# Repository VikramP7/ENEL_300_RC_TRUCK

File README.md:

*<div align="right"> Vikram Procter, Caleb Garcia, Graham Coleman, Devon Calvin | Feb 12, 2025 </div>*

# DIDSBURY DIDDLERS & Co. Est. 2006 - README

## Project Overview

Remote control car for our ENEL 300 design class at the Schulich School of Engineering at University of Calgary.

Our car integrates a variety of features including distance measurement, metal detection, togglable head/tail lights, tank steering, and more. These features are implemented through 3 custom PCBs, designed in Altium or KiCad. Wireless locomotion control and light control is implemented using the HC-05 Bluetooth transceiver module. The physical design was inspired by a RAM 3500 Cummins 6.7 Twin Turbo and its stereotypical owner *(Devon)*. This allowed us to bring a part of Alberta culture to the academic environment through innovation and design.

## Team Dynamic
  
*Image of Team Members and Professors: Dr. Philippe Gray, Devon Calvin, Graham Coleman, Vikram Procter, Caleb Garcia, and Dr. Flavio Alegretti Ramos; respectively from left to right*

The workload of the various systems was divided amongst us based on interest and skill. Coleman was responsible for implementing metal detection and distance measurement, in addition to working on Bluetooth communications, and controller design. Procter was responsible for ECU, power regulation, inter-board communication, general code management and review. Garcia was responsible for software development, 3D design and printing, and product selection. Calvin was responsible for motor driver development, 3D design, and Bluetooth communications.

## Systems Overview

The block diagram shows the operating architecture of the RC truck describing the PCB boards connections to each other. There were four custom PCBs in which 3 were used in the final design. Each board design function and integration are described in detail in the sections bellow. 

All boards excluding the controller interface with each other using an I2C bus, the ECU acts as the master on the bus and the Sensor Board/Motor Control Board act as slaves on the bus. The Controller board interfaces with the ECU alone using USART over a Bluetooth connection.

The four boards include: 
- **Controller Board** | not utilized in the final design, but would have been used within the controller to offer UI to user.
- **ECU** | Electronics Control Board, acts to integrate functionality of all other boards along with power supply regulation.
- **Sensor Board** | Finds and relays metal detection and distance sensing data.
- **Motor Control Board** | Houses motor drivers and receives data for locomotion control of vehicle.

## Sensors Systems (Sensor Board)
### Metal Detector

The metal detection system is designed around a 555 timer IC and inductor capacitor (LC) circuit. The 555 timer produces an AC input in which the frequency response output varies with changes in inductance. By exposing the inductor coil placed on the bottom of the car to a copper sheet the inductance of the coil changes and the frequency of the output changes in response.

The sensor board uses a built in timer module of the AVR128DB28 to measure the frequency of the LC circuit. By tuning a threshold, the recorded frequency could be used to identify if the coil was exposed to metal. This information was then relayed over I<sup>2</sup>C to the ECU.

### Distance Sensor
An ultrasonic distance sensor was used to find the distance of the nearest object in front of the car. The Sensor Board interfaced with the ultrasonic providing the appropriate 10 microsecond trigger and recording the echo. This raw echo data was transmitted over I<sup>2</sup>C to the ECU.

*Render of Sensor Board PCB*

## Power Systems (ECU)
### Battery
The battery we selected has a capacity of 3000 mAh with a nominal voltage of 12.6V, this was used to supply power to all boards and the motors excluding the metal detection circuit. This battery consisted of 4 cells with integrated charging and level balancing technology.

Through estimates of maximum current draw, the runtime on one full charge was calculated to be 228 minutes. This battery was initially chosen as previously we had sourced higher power motors; these higher power motors made the battery selection more reasonable for runtime calculations. However, in switching motors we decided not to change our battery selection as it was still sufficient for operation.

### Voltage Regulation

*Custom Standard for Molex Connector*

To produce the voltage 5V and 3.3V lines linear dropout regulators (LDOs) were used. These regulators were placed on the ECU and using a custom Molex connector, voltage levels were distributed to other boards (motor control board, and sensor board).

### Power Switch
The power switch uses a PMOS high side switch topology to switch between three states: off, USB power, and battery power. For regular operation 12.6V battery is used, however for development and debugging 5V USB can be used. This switch system allows for isolation between the battery and USB for safe operation.

  *Image of ECU Showing Power Switch*

## Communications Systems (ECU + Others)
### Bluetooth USART

[*Image Cred.*](https://www.electronicwings.com/sensors-modules/bluetooth-module-hc-05-)

The ECU board and controller boards preformed wireless communications via a USART over Bluetooth communications module [HC-05](https://www.electronicwings.com/sensors-modules/bluetooth-module-hc-05-). The controller board would send movement control and light switch position data to the ECU board, describing positions of single axis joy sticks and if the lights should be on or not. The ECU board would send sensor data including distance and metal detection.

Three 8-bit data packets were sent from the controller. Two packets described the left and right joystick position encoded using sign magnitude. And the third packet contained the status of the light switch. 

One 8-bit packet was sent from the ECU to describe metal detection (most significant bit), and distance sensor data encoded in the 7 least significant bits. 

### I<sup>2</sup>C Inter-board Communication
An I<sup>2</sup>C bus was utilized between boards within the vehicle (ECU, Motor Board, and Sensor Board). Connection between boards was accomplished using the same custom Molex connector as described in the power regulation section.

The ECU hosted the I<sup>2</sup>C bus housing the pull-up resistors and acted as the master on the bus. The ECU would relay motor control data received from the controller board to the Motor Board. The ECU would request data from the Sensor Board, receiving distance and metal detection data. I<sup>2</sup>C communications is a non-blocking function within the super loop of all boards. 

I<sup>2</sup>C packets took a very similar form to USART packets over Bluetooth. The motor board would receive two 8-bit sign-magnitude packets one for each side of the vehicle. Two packets were received from the Sensor Board. The MSB of the first packet described the metal detection data, and the remaining 15 bits described the distance sensor data. The ECU would compress the data to 7 bits before relaying to the controller.

*Image of ECU PCB*

## Controller

*3D Model of Controller*

### LCD UI
The 2x16 ASCII LCD selected was equipped with an I<sup>2</sup>C piggy-back-board to allow for fewer required pins for operation. The controller board acted as the master and LCD as slave on the I<sup>2</sup>C bus.

On power up the LCD would display the team name, before displaying the distance data, and metal detection data Custom functions were written to interface with the LCD to allow for ease of formatting the results on the screen, while avoiding having to do floating point calculations. 

### Inputs
The controller was equipped with two single axis joysticks for controlling locomotion and one switch for controlling the lights. The vehicle utilized a tank steering system where each joystick would control the speed of the wheels on one side of the vehicle. The joysticks function as a potentiometer, by creating a voltage divider the change in resistance as the joystick moved was recorded using an ADC on the AVR128DB28. Through the careful design of the voltage divider the AVR128DB28 was able to provide ADC input to a much higher accuracy than needed (12-bit resolution). This value was compressed and encoded to the 8-bit sign-magnitude value transmitted over I<sup>2</sup>C.

Data collected through the input devices and data required for displaying on the LCD was transmitted using USART over Bluetooth using the [HC-05](https://www.electronicwings.com/sensors-modules/bluetooth-module-hc-05-). Although data was compressed for transmission over Bluetooth, it was done in a way that retains accuracy to the level required by the project.   

*A PCB was designed for the controller however due to time and resource constraints the PCB was not assembled and the controller board was constructed using a perfboard*

## Locomotion Systems (Motor Board)

The selected motors are driven using two L298N H-Bridge motor drivers, using 12.6V supplied from the battery with inline Toshiba TCKE812NA E-Fuses for over current protection. As this is a high current board, large polygon pours were used when dealing with high current nets. Thermal reliefs were also removed to improve thermal conduction during operation and max current tolerance. As this board interfaces with large inductive loads, fly back diodes were also used. 

The Motor Control Board is also equipped with an AVR128DB28 to interface with the I<sup>2</sup>C bus and use information received to operate the motor driver ICs. The Motor Control Board receives two 8-bit packets containing the sign-magnitude values for the speeds the motors should be spinning on each side of the vehicle. To control the motor speed a PWM signal generated using the AVR128DB28 was used as an input to the enable pin of the L298N motor drivers. The 8-bit packets are decoded to find the polarity (from sign) and duty of PWM (from magnitude). 

## Mechanical Design
The frame and body of the vehicle, along with the controller case was 3d printed. The frame consisted of a baseplate that custom motor bracket mounts were attached to. The frame had holes drilled for connections to motor terminals. The body was printed from a modified 3d model of a RAM 3500 found online. Wheels were also printed and off the shelf rubber tires were fitted to them. All 3d models were scaled to achieve an approximate 1:16 scale to the real truck. All prints were done in PLA, and infill was scaled based on points of high stress.  

*3D Printed Body File*

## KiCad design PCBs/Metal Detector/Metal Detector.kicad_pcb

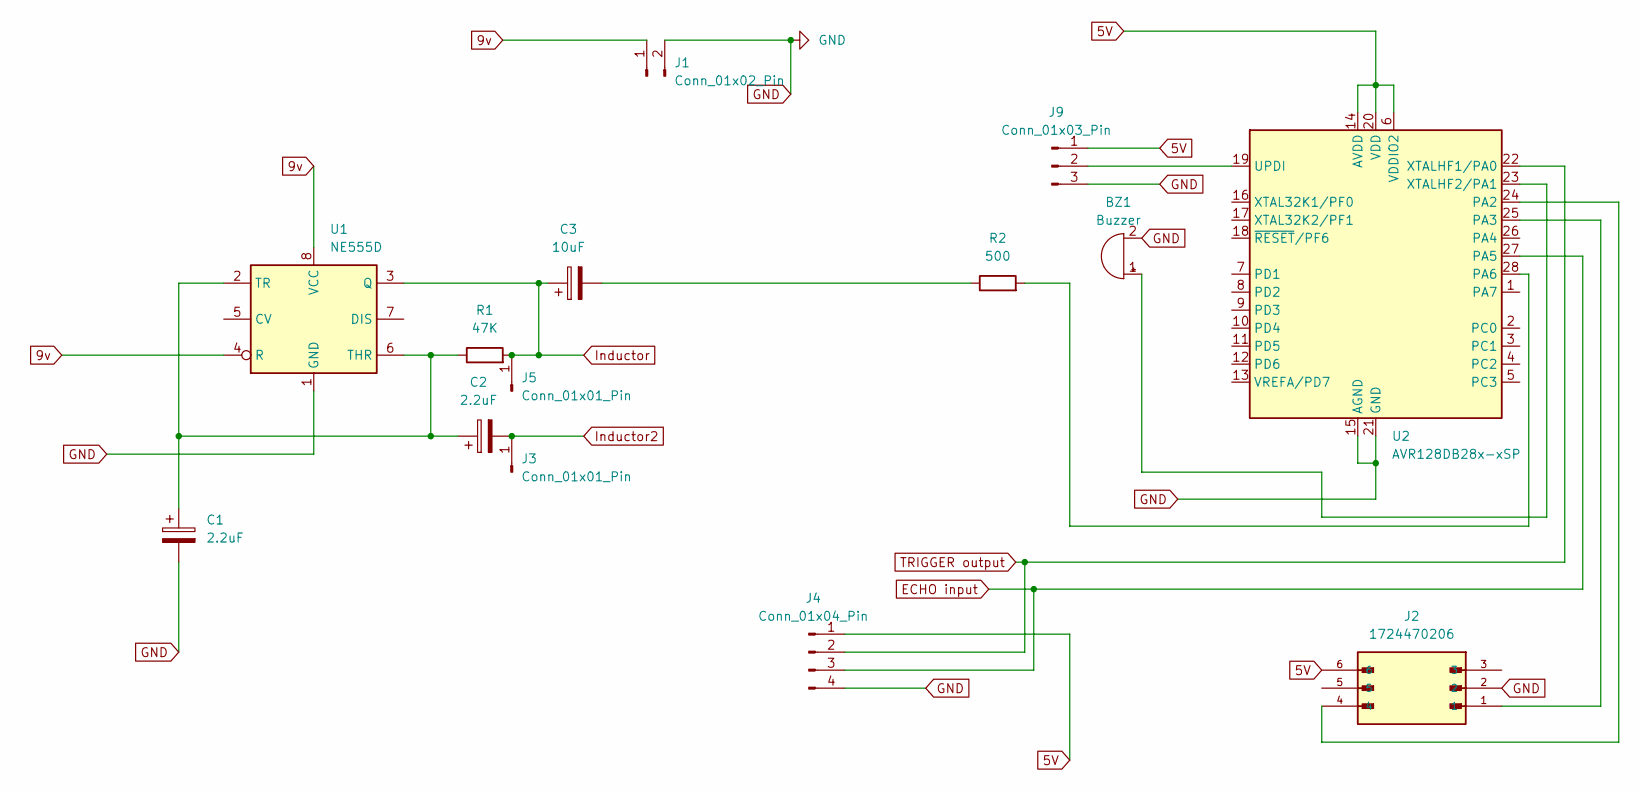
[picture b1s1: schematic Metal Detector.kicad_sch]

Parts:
BZ1: Buzzer; Buzzer_TDK_PS1240P02BT_D12.2mm_H6.5mm
C1, C2: 2.2uF; CP_Radial_D8.0mm_P2.50mm
C3: 10uF; CP_Radial_D8.0mm_P2.50mm
J1: Conn_01x02_Pin; PinHeader_2x01_P2.54mm_Vertical
J2: 1724470206; MOLEX_1724470206; PARTREV A6
J3, J5: Conn_01x01_Pin; PinSocket_1x01_P2.54mm_Vertical
J4: Conn_01x04_Pin; PinHeader_1x04_P2.54mm_Vertical
J9: Conn_01x03_Pin; PinHeader_1x03_P2.54mm_Vertical
R1: 47K; R_Axial_DIN0309_L9.0mm_D3.2mm_P12.70mm_Horizontal
R2: 500; R_Axial_DIN0309_L9.0mm_D3.2mm_P12.70mm_Horizontal
U1: NE555D; P8
U2: AVR128DB28x-xSP; SPDIP28_SP_MCH

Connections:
5V: J2.6, J4.1, J9.1, U2.6 (VDDIO2), U2.14 (AVDD), U2.20 (VDD)
9v: J1.1, U1.4 (R), U1.8 (VCC)
ECHO input: J4.3, U2.27 (PA5)
GND: BZ1.2 (-), C1.2, J1.2, J2.2, J4.4, J9.3, U1.1 (GND), U2.15 (AGND), U2.21 (GND)
Inductor: C3.1, J5.1, R1.2, U1.3 (Q)
Inductor2: C2.2, J3.1
unnamed: BZ1.1 (+), U2.23 (XTALHF2/PA1)
unnamed: C3.2, R2.1
unnamed: J9.2, U2.19 (UPDI)
unnamed: C1.1, C2.1, R1.1, U1.2 (TR), U1.6 (THR)
unnamed: J2.4, U2.24 (PA2)
unnamed: J2.1, U2.25 (PA3)
unnamed: R2.2, U2.28 (PA6)
TRIGGER output: J4.2, U2.22 (XTALHF1/PA0)

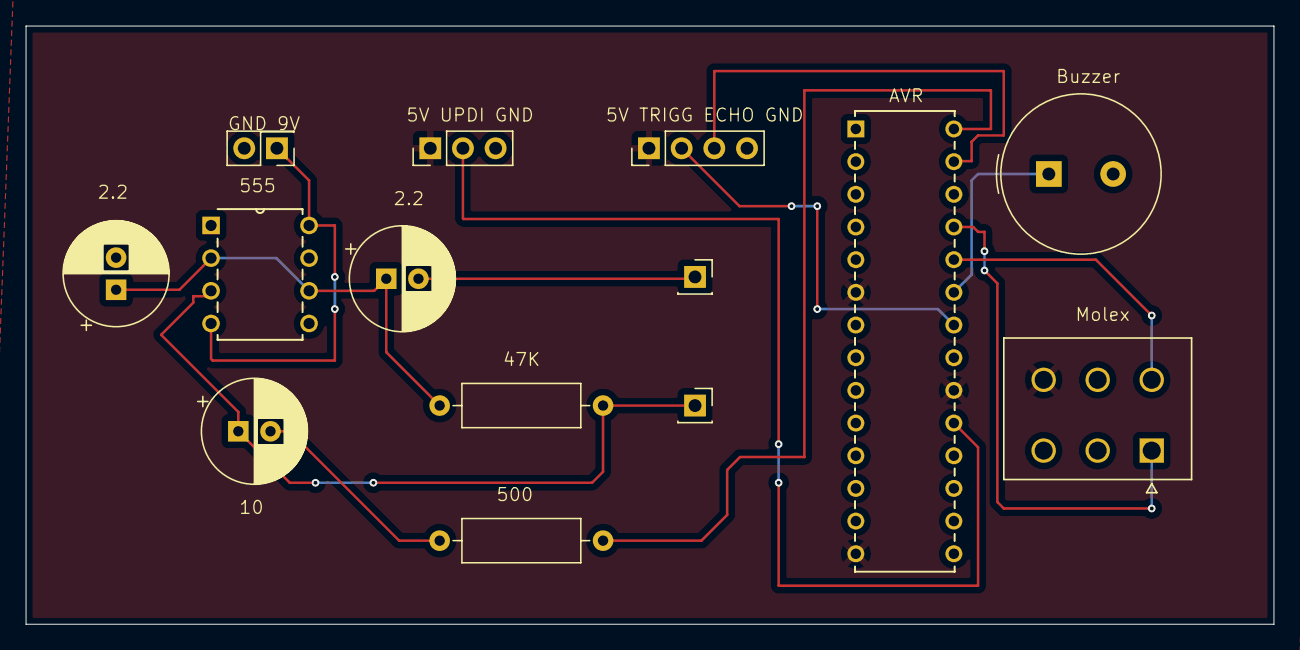
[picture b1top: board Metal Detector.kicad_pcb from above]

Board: 2 copper layers, 97.0 x 46.5 mm, 14 parts (0 on the bottom side), 14 nets.

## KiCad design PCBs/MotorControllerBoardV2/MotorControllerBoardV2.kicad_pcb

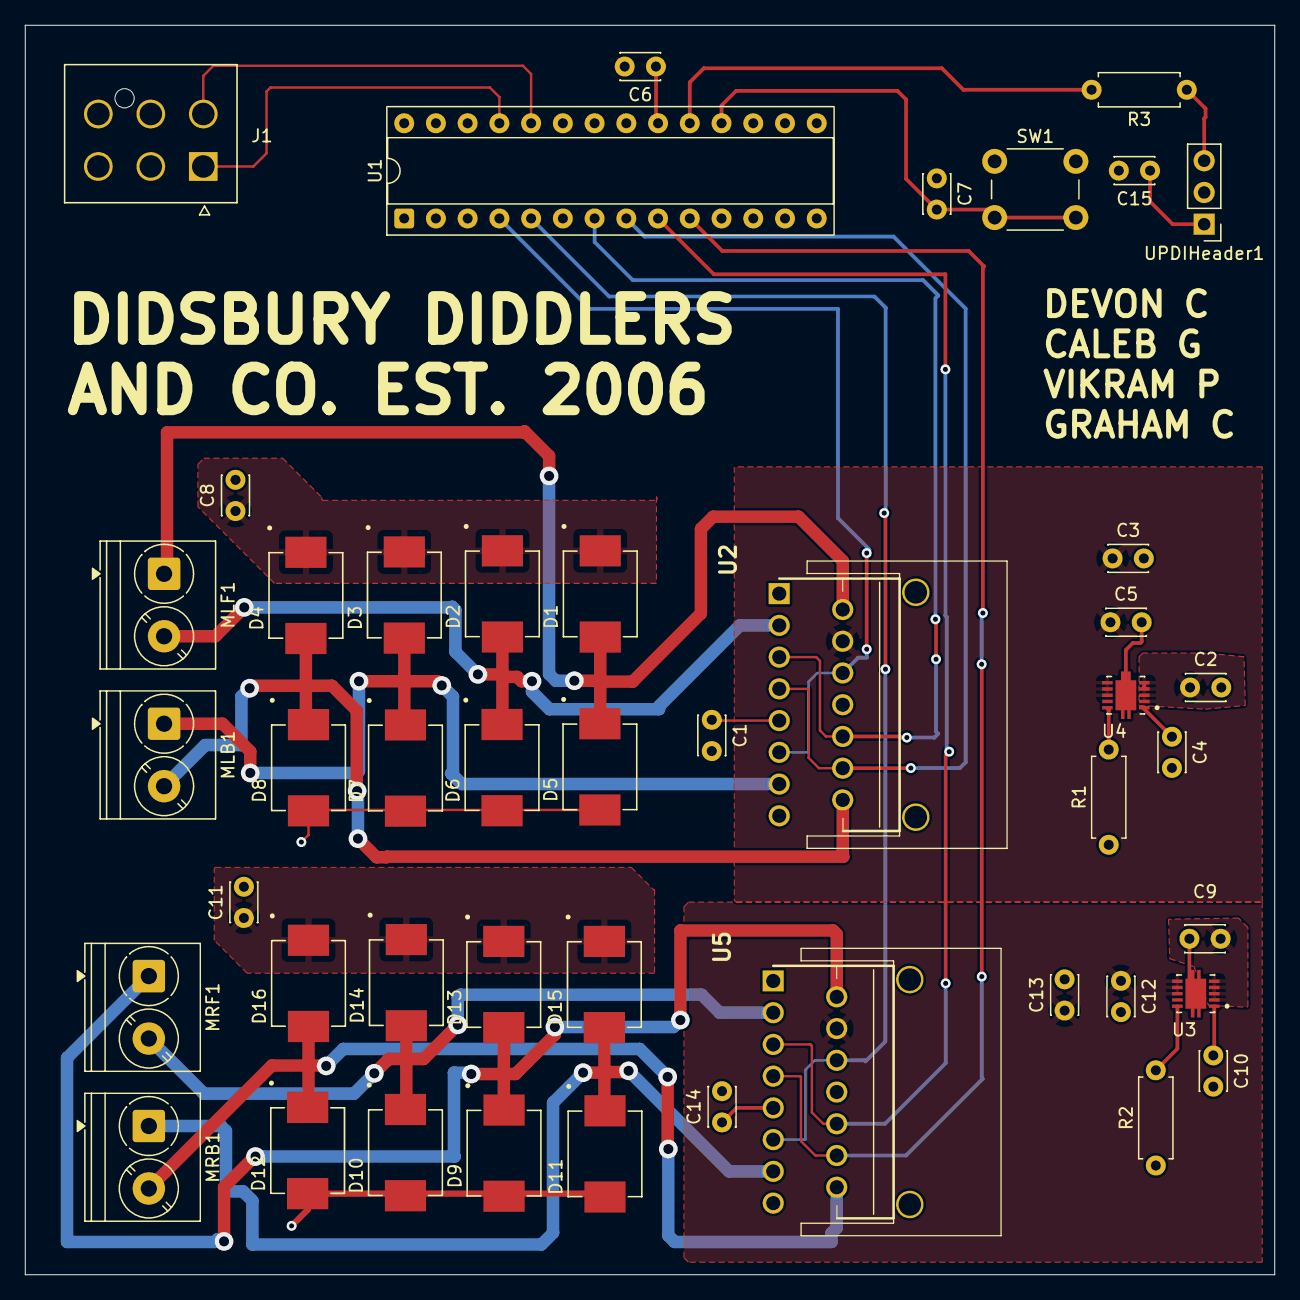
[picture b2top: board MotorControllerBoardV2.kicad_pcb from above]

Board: 4 copper layers, 100.0 x 100.0 mm, 46 parts (0 on the bottom side), 28 nets.

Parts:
C1, C5, C13, C14: 100nF; C_Disc_D3.0mm_W2.0mm_P2.50mm
C2, C3, C6, C7, C9, C12, C15: 1μF; C_Disc_D3.0mm_W2.0mm_P2.50mm
C4, C10: 1nF; C_Disc_D3.0mm_W2.0mm_P2.50mm
C8, C11: 220μF; C_Disc_D3.0mm_W2.0mm_P2.50mm
D1, D2, D3, D4, D5, D6, D7, D8, D9, D10, D11, D12, D13, D14, D15, D16: B340-13-F; DIO_B340-13-F
J1: 2125201006; MOLEX_2125201006
MLB1: Screw_Terminal_2_P5.00mm; TerminalBlock_Phoenix_PT-1,5-2-5.0-H_1x02_P5.00mm_Horizontal
MLF1: Screw_Terminal_2_P5.00mm; TerminalBlock_Phoenix_PT-1,5-2-5.0-H_1x02_P5.00mm_Horizontal
MRB1: Screw_Terminal_2_P5.00mm; TerminalBlock_Phoenix_PT-1,5-2-5.0-H_1x02_P5.00mm_Horizontal
MRF1: Screw_Terminal_2_P5.00mm; TerminalBlock_Phoenix_PT-1,5-2-5.0-H_1x02_P5.00mm_Horizontal
R1, R2: 54.5k; R_Axial_DIN0207_L6.3mm_D2.5mm_P7.62mm_Horizontal
R3: 1.2k; R_Axial_DIN0207_L6.3mm_D2.5mm_P7.62mm_Horizontal
SW1: SW_Push; SW_PUSH_6mm
U1: AVR128DB28x-xSP; DIP-28_W7.62mm_Socket
U2, U5: L298N; Multiwatt15L V with heatsink v2
U3, U4: TCKE812NA_RF; IC_TCKE812NA_RF
UPDIHeader1: PINHD_1x3_Male; PinHeader_1x03_P2.54mm_Vertical

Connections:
5V Logic: C1.1 (+), C6.1 (+), C14.1 (+), C15.1 (+), J1.6, U1.6 (VDDIO2), U1.14 (AVDD), U1.20 (VDD), U2.9 (Vss), U5.9 (Vss), UPDIHeader1.1
7.2V Motor: C2.1 (+), C8.1 (+), C9.1 (+), C11.1 (+), D1.C, D2.C, D3.C, D4.C, D13.C, D14.C, D15.C, D16.C, J1.3, U3.2 (EN/UVLO), U3.3 (VIN), U3.4 (VIN), U3.5 (VIN), U4.2 (EN/UVLO), U4.3 (VIN), U4.4 (VIN), U4.5 (VIN)
GND: C1.2 (-), C2.2 (-), C3.2 (-), C4.2 (-), C5.2 (-), C6.2 (-), C7.1 (+), C8.2 (-), C9.2 (-), C10.2 (-), C11.2 (-), C12.2 (-), C13.2 (-), C14.2 (-), C15.2 (-), D5.A, D6.A, D7.A, D8.A, D9.A, D10.A, D11.A, D12.A, J1.2, R1.1 (+), R2.1 (+), SW1.1, U1.15 (AGND), U1.21 (GND), U2.1 (SENSE_A), U2.8 (GND), U2.15 (SENSE_B), U3.11 (GND), U4.11 (GND), U5.1 (SENSE_A), U5.8 (GND), U5.15 (SENSE_B), UPDIHeader1.2
LBWD: U1.8 (PD2), U2.7 (IN2), U2.12 (IN4)
LFWD: U1.7 (PD1), U2.5 (IN1), U2.10 (IN3)
LPWM: U1.4 (PC2), U2.6 (EnA), U2.11 (EnB)
unnamed: C3.1 (+), C5.1 (+), U2.4 (Vs), U4.6 (VOUT), U4.7 (VOUT), U4.8 (VOUT)
unnamed: C4.1 (+), U4.1 (DV/DT)
unnamed: C7.2 (-), SW1.2, U1.18 (~RESET/PF6)
unnamed: C10.1 (+), U3.1 (DV/DT)
unnamed: C12.1 (+), C13.1 (+), U3.6 (VOUT), U3.7 (VOUT), U3.8 (VOUT), U5.4 (Vs)
unnamed: R1.2 (-), U4.10 (ILIM)
unnamed: R2.2 (-), U3.10 (ILIM)
unnamed: R3.1 (+), UPDIHeader1.3
unnamed: R3.2 (-), U1.19 (UPDI)
unnamed: D1.A, D5.C, MLF1.1, U2.2 (OUT1)
unnamed: D2.A, D6.C, MLF1.2, U2.3 (OUT2)
unnamed: D3.A, D7.C, MLB1.1, U2.13 (OUT3)
unnamed: D4.A, D8.C, MLB1.2, U2.14 (OUT4)
unnamed: D9.C, D13.A, MRF1.1, U5.2 (OUT1)
unnamed: D10.C, D14.A, MRF1.2, U5.3 (OUT2)
unnamed: D11.C, D15.A, MRB1.1, U5.13 (OUT3)
unnamed: D12.C, D16.A, MRB1.2, U5.14 (OUT4)
RBWD: U1.10 (PD4), U5.7 (IN2), U5.12 (IN4)
RFWD: U1.9 (PD3), U5.5 (IN1), U5.10 (IN3)
RPWM: U1.5 (PC3), U5.6 (EnA), U5.11 (EnB)
SCL: J1.1, U1.25 (PA3)
SDA: J1.4, U1.24 (PA2)

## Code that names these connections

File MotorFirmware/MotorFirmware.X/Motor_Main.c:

#include <xc.h>

//******************************************************************************

// avr128db48-bare-metal-twi-mplab Main Initialization

//******************************************************************************

#include <avr/io.h>
#include <avr/interrupt.h>
#include <avr/eeprom.h>

#include "peripherals/CLKCTRL/CLKCTRL.h"
#include "peripherals/TWI/TWI_client.h"
#include "TWI_blockData.h"

#define DATA_SIZE 16

#define AVERAGE_SIZE 4

#define RIGHT 1
#define LEFT 0

//******************************************************************************

// Didsbury Diddlers Proprietary Function Definitions

//******************************************************************************

// Fairly sure that his clock setup is handled in the library

//// === CLOCK SETUP ===
//void setup_clock() {
//    CCP = 0xD8;
//    CLKCTRL.OSCHFCTRLA = 0b00010100;      // Set 16 MHz internal oscillator
//    while (CLKCTRL.MCLKSTATUS & 0b00000001); // Wait for clock switch to complete
//}

// Lowkey might need to readdress the pin setup, I have to fucking clue what
// the library is doing rn.

// === PIN SETUP ===
void setup_pins() {
    PORTMUX.TCAROUTEA = 0b00000010;
    PORTC.DIRSET = 0b00001100;            // PC2 (TCB0), PC3 (TCB1) as PWM outputs
    PORTD.DIRSET = 0b00011110;            // PD1–PD4 as motor direction control outputs
}

// === PWM SETUP ===
void setup_pwm() {
    TCA0.SPLIT.CTRLESET = 0b00001100;
    TCA0.SPLIT.CTRLD = 0b00000001;
    TCA0.SPLIT.LPER = 0xff;
    TCA0.SPLIT.HPER = 0xff;
    
    TCA0.SPLIT.HCMP0 = 0x00; // for right pwm, PC3
    TCA0.SPLIT.LCMP2 = 0x00; // for left pwm, PC2
    
    TCA0.SPLIT.CTRLB = 0b00010100;
    
    TCA0.SPLIT.CTRLA = 0b00000001;
    
}

// === MOTOR CONTROL FUNCTION ===
void drive_motor(uint8_t sm, uint8_t side) {
    uint8_t sign = sm & 0x80;             // Bit 7 = direction
    uint8_t magnitude = sm & 0x7F;        // Bits 6–0 = speed

    if(side == RIGHT){
        if (sign) {
            PORTD.OUTSET = (1 << 4);    // Set backward pin high
            PORTD.OUTCLR = (1 << 3);    // Clear forward pin
        } 
        else {
            PORTD.OUTSET = (1 << 3);    // Set forward pin high
            PORTD.OUTCLR = (1 << 4);    // Clear backward pin
        }
        // set PWM duty 0-ff for right side
        TCA0.SPLIT.HCMP0 = magnitude << 1;
    }
    else if (side == LEFT){
        if (sign) {
            PORTD.OUTSET = (1 << 2);    // Set backward pin high
            PORTD.OUTCLR = (1 << 1);    // Clear forward pin
        } else {
            PORTD.OUTSET = (1 << 1);    // Set forward pin high
            PORTD.OUTCLR = (1 << 2);    // Clear backward pin
        }
        // set PWM duty 0-ff for right side
        TCA0.SPLIT.LCMP2 = magnitude << 1;
    }
}

//******************************************************************************

// Main

//******************************************************************************

// === MAIN LOOP ===
int main(void) {
    
    setup_pins();                         // Set up direction and PWM pins
    setup_pwm();                          // Configure PWM for TCB0 and TCB1
       
    //Setup CPU Clocks
    CLKCTRL_init();
    
    //Setup TWI I/O
    TWI_initPins();
    
    //Setup TWI Interface
    TWI_initClient(0x11);
    
    //Data to R/W to. (Must be volatile)
    volatile uint8_t data[DATA_SIZE];
    
    //Initialize Memory to 0x00
    for (uint8_t i = 0; i < DATA_SIZE; i++)
    {
        data[i] = 0x00;
    }
    
    //Attach R/W Buffers
    //Note: The buffers can be separated, or they can be the same memory, if desired.
    setupReadBuffer(&data[0], 16);
    setupWriteBuffer(&data[8], 8);
    
    //Assign ISRs to Block Memory Library
    TWI_assignByteWriteHandler(&_TWI_StoreByte);
    TWI_assignByteReadHandler(&_TWI_RequestByte);
    TWI_assignStopHandler(&_onTWIStop);
    
    //Enable Interrupts
    sei();

//******************************************************************************
    
  // Super Loop  

//******************************************************************************
    
    // Responsible for motor control from ECU I2C data. Sending left then right
    // motor data.
    static uint8_t rightAve[AVERAGE_SIZE] = {0};
    static uint8_t leftAve[AVERAGE_SIZE] = {0};
    static uint8_t aveIndex = 0;
    static uint8_t rightSpeed = 0;
    static uint8_t leftSpeed = 0;
    
    while (1)
    {
        /*
        leftAve[aveIndex] = data[8];
        rightAve[aveIndex] = data[9];
        aveIndex++;
        aveIndex %= AVERAGE_SIZE;
        
        for (uint8_t i = 0; i < AVERAGE_SIZE; i++){
            if(leftAve[i] & 0b10000000){
                leftSpeed -= (leftAve[i] & 0b011111111);
            }else {
                leftSpeed += (leftAve[i] & 0b011111111);
            }

            if(rightAve[i] & 0b10000000){
                rightSpeed -= (rightAve[i] & 0b011111111);
            }else {
                rightSpeed += (rightAve[i] & 0b011111111);
            }
        }
        
        rightSpeed >> 2;
        leftSpeed >> 2;
         */
        
        drive_motor(data[8], LEFT);   // PD1 = FWD, PD2 = BWD (left)
        drive_motor(data[9], RIGHT);  // PD3 = FWD, PD4 = BWD (right)
    }
}

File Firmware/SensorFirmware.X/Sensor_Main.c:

#include <xc.h>

//******************************************************************************

// avr128db48-bare-metal-twi-mplab Main Initialization

//******************************************************************************

#include <avr/io.h>
#include <avr/interrupt.h>
#include <avr/eeprom.h>

#include "peripherals/CLKCTRL/CLKCTRL.h"
#include "peripherals/TWI/TWI_client.h"
#include "TWI_blockData.h"

#define DATA_SIZE 16

#define VALUE_U_SIZE 8

/* --------- GLOBAL VARS DECLARATION ------------- */
uint16_t value_u[VALUE_U_SIZE];
uint8_t value[5];
uint8_t count_u = 0;
uint8_t tally_u = 0;
uint8_t count = 0;
uint8_t tally = 0;
//uint8_t duty = 25000;
float distance = 0.0;
float distance_final = 0.0;

//Data to R/W to. (Must be volatile)
volatile uint8_t data[DATA_SIZE];

void SensorInitialization(){
    PORTA.DIRSET = 0b00000011;   //PA0 and PA1 set as output
    TCA0.SINGLE.CTRLA = (0x01)<<3 | 0x01;//divide by 16 and enable clk
    TCA0.SINGLE.CTRLB = 0x03;   //single slope PWM
    TCA0.SINGLE.CTRLB |= 0x01 << 4; //PA0 enabled
    TCA0.SINGLE.PER = 31249; //value calculated to produce trigger pulse
    TCA0.SINGLE.CMP0 = 6; //set to very low duty for trigger pulse
    EVSYS.CHANNEL0 = 0x45;    //PORTA pin PA5 as echo input
    EVSYS.USERTCB2CAPT = 0x01;  //Choose channel 0
    TCB2.INTCTRL = 0x01; //Capture interupt enable
    TCB2.EVCTRL = 0x01; //enable input capture event
    TCB2.CTRLB = 0x04; //PWM measurement mode
    TCB2.CTRLA = 0x01; //TCB enable
    EVSYS.CHANNEL1 = 0x46;    //PORTA pin PA6 for metal detector
    EVSYS.USERTCB1CAPT = 0x02;  //Choose channel 1
    TCB1.INTCTRL = 0x01; //Capture interupt enable
    TCB1.EVCTRL = 0x01; //enable input capture event
    TCB1.CTRLB = 0x03; //Frequency measurement mode
    TCB1.CTRLA = 0x01; //TCB enable
}

/* ------ Define ISR -----*/
ISR(TCB2_INT_vect){
    TCB2.INTFLAGS = 0x01; //clears flag
    TCA0.SINGLE.CMP0 = 6;
    value_u[count_u] = TCB2.CCMP;
    count_u++;
    count_u %= VALUE_U_SIZE; // used later to average TCB.CCMP for distance measuring
    long averageDist = 0;
    //RMS might be appropriate for emphasizing the larger values.
    for (int i = 0; i < VALUE_U_SIZE; i++){
       averageDist += value_u[i]; //averages TCB.CCMP for distance measuring
    }
    averageDist = averageDist >> 3;
    data[0] = (averageDist & 0xFE) | (data[0] & 0b00000001);
    data[1] = averageDist >> 8;
}

ISR(TCB1_INT_vect){
    TCB1.INTFLAGS = 0x01; //clears flag
    value[count] = TCB1.CCMP;
    if(value[count] < 200){ 
        tally++;
    }
    count++;
    if(count >= 5){ //if five consecutive values read metal, detect the metal.
        if(tally == 5){
            PORTA.OUT = 0b00000010; 
            data[0] |= 0x01;
        }else{
            PORTA.OUT = 0b00000000;
            data[0] &= 0xFE;
        }
        count = 0;
        tally = 0;
    }
}

// === MAIN FUNCTION ===
int main(void) {
    //Setup CPU Clocks
    CLKCTRL_init();
    
    // Sensor Initialization
    SensorInitialization();
    
    //Setup TWI I/O
    TWI_initPins();
    
    //Setup TWI Interface
    TWI_initClient(0x22); // Initialize client address as 0x22
    
    
    //Initialize Memory to 0x00
    for (uint8_t i = 0; i < DATA_SIZE; i++)
    {
        data[i] = 0x00;
    }
    
    //Attach R/W Buffers
    //Note: The buffers can be separated, or they can be the same memory, if desired.
    setupReadBuffer(&data[0], 16);
    setupWriteBuffer(&data[8], 8);
    
    //Assign ISRs to Block Memory Library
    TWI_assignByteWriteHandler(&_TWI_StoreByte);
    TWI_assignByteReadHandler(&_TWI_RequestByte);
    TWI_assignStopHandler(&_onTWIStop);
    
    //Enable Interrupts
    sei();
    
    while (1)
    {   
    }
}

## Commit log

2025-04-02 Radio Test
2025-04-02 Created this file
    BALLS!
2025-04-02 Added Initial commit for ecu firmware file
2025-04-02 Started doing radioSPI driver
2025-04-02 Radio Datasheet
2025-04-02 Added COde
2025-04-03 Re arranged initializations
2025-04-03 addded stuff
2025-04-04 SPI Radio Stuff
2025-04-05 small change with function naming
2025-04-05 Updated radio SPI
2025-04-05 changed clock
2025-04-05 lkjhkj
2025-04-05 Updated radio lib
2025-04-05 Added Test code for radio
2025-04-05 ranom build
2025-04-05 Path cooked
2025-04-05 fixed stuffs
2025-04-05 buld crap
2025-04-05 push crap
2025-04-06 Did Things
2025-04-07 CreatedControllerFirmware
2025-04-07 Updated SPI radio to hopefully function
2025-04-07 Locals
2025-04-08 Fixing SS
    Fixed SS by moving transfer stalls
2025-04-08 It FUCKING works!!
2025-04-08 Removed old reference files
2025-04-08 Deleted Temp
2025-04-08 Created I2C Library Prototype
2025-04-09 I2C Libraries
2025-04-09 I2C config
2025-04-19 Not Cooked Main ;)
2025-04-19 Updated clock frequency
2025-04-19 Local Type Shit
2025-04-19 Loccals
2025-04-19 Potential Motor Data Transfer
2025-04-19 Starting the index at only the write data portion
2025-04-19 Type shit
2025-04-19 I/O Expander Null
2025-04-19 idk amn
2025-04-20 It works now
2025-04-20 Added ECU firmware
2025-04-20 Removed old controller code
2025-04-20 Added Sensor board
2025-04-20 Added Sensor Board Code
2025-04-20 Fixed weird issue
2025-04-20 Sensor board works!
2025-04-21 Comments on RMS
2025-04-21 Random local changes
2025-04-21 controller type shit
2025-04-21 created LCD library
2025-04-21 Motor, Sensor, and Controller Integration
2025-04-21 Fixed some controller firmware
2025-04-22 Added some Comments
    Fixed the boot sequence, optimized some code, and added comments.
2025-04-22 Switch works
2025-04-22 line
2025-04-22 Added stuff to the ECU main for Bluetooth
2025-04-22 edited ECU
2025-04-23 Fixed ECU
2025-04-23 Removed unnecessary files
2025-04-23 Added function description
2025-04-23 Removed the boot sequence
2025-04-23 Removed unused buzzer firmware
2025-04-23 Clean up
2025-04-23 Moved everthing to new folders
2025-04-23 AddedMyPCBs
2025-04-23 Changed folder name
2025-04-23 Added Comments
2025-04-23 formatting
2025-04-23 added expeditiously
2025-04-23 Removed useless buzzer firmware
2025-04-23 Made comments for main
2025-04-23 Edit comments
2025-04-23 Edited comments
2025-04-23 Metal Detector
2025-04-23 Added Devons PCB
2025-04-23 Removed file I guess
2025-04-25 Changed Readme
2025-05-02 Added more to readme
2025-05-02 Small add to readme
2025-05-04 Added more to About ECU to ReadME
2025-05-04 Added Controller Stuff to README
2025-05-04 Added Images to README
2025-05-04 Added Images of README
2025-05-04 Added caption to image
2025-05-04 Added More Picture and Videos
2025-05-04 Small formatting Edit
2025-05-04 Spell Checked
2025-05-04 Added Image Cred
2025-05-08 Added image captions
